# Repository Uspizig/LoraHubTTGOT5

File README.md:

# LoraHubTTGOT5
Please keep in mind. There are some Limitations in the TTn network right now:
1. For usage with TTN V3: Pease consider this change to avoid unwanted Downlink messages. https://github.com/mcci-catena/arduino-lmic/issues/713 

(Prerequisite: This is my Hobby: No Guarantee for HW or SW. I do not take any responsibility or will help you. This is: "Take it as it is or leave it".)
DO NOT USE THIS in ANY COMMERCIAL PRODUCTS

A LORA TTN Daughter Board for a TTGO T5 Board (http://s.click.aliexpress.com/e/NPRqgBkG) with BME680, BME280, CCS811 and connection possibilities for several other I²C Boards

You might have seen several E-Ink Boards from Waveshare lately. I came across some Boards from TTGO with an ESP32 lately on Aliexpress.
While experimenting with these Boards I tought: Why not add a LORA TTN Chip to these Boards and some other environment sensors.

So here is my try:

You may find in this Repository:
1. Hardware: KiCad & Gerber Files for 
2. SMT Assembly Files for jlcPCB 
3. Pinning: Pin Description
4. Software: A how to make these things running relatively easy in an Arduino IDE

What you need to do to get the SW Running:
1. Clone this Git: https://github.com/ZinggJM/GxEPD2 and install to your Arduino lib folder
2. Replace the two files with the ones provided in GxEPDReplace
3. Install: https://github.com/thesolarnomad/lora-serialization
4. Clone this Git: https://github.com/mcci-catena/arduino-lmic
5A. Make the modifications mentioned in otta SW
5B. Edidt config in the MCCI-Catena to set according yoru Country.
6. Get an App ID, from Thethingsnetwork
7. Check if your area has LORA TTN Coverage
8. Try out one of the examples.

What you need to get the HW:
- TTGO T5 EPaper Board: https://de.aliexpress.com/item/32869729970.html
- RFM95 Lora Chip: https://de.aliexpress.com/item/32831799362.html
- Antenna Connector SMA: http://s.click.aliexpress.com/e/5oGOCiY0
- (OPTIONAL)8dBi Antenna 868MHz: http://s.click.aliexpress.com/e/KVkmsTGG
- (OPTIONAL)TPL5110 for Low Power: http://s.click.aliexpress.com/e/EA7q1R48
- Spacer-Screws: http://s.click.aliexpress.com/e/KejkugSM

Hub Board:
1. Download the Gerber and BOM Files
2. Upload to JLCPCB
3. Select SMT Assembly
4. Solder 3 Diodes, Antenna Connector and RFM Module on the Board
5. (Optional): Solder Battery Connector and TPL5110 Chip on the Board.
6. I made a mistake on the FET and switched Drain and Source pin. You need to make a air wire to fix this if you want to use the TPL5110 RTC.

What you need to Solder
1. RFM95 Chip
2. Antenna Connector
3. 3x Diodes
(Optional) TPL5110 Chip and Battery Connector

Housings:
https://www.thingiverse.com/thing:3462483
https://www.thingiverse.com/thing:4055993

Useful Equipment.:
- Soldering Iron TS100: http://s.click.aliexpress.com/e/Eq2v9g12
- USB Cable: http://s.click.aliexpress.com/e/NiloJfUM
- Soldering Mat. http://s.click.aliexpress.com/e/NAoYAQ5K

My projects are influenced by Dave(G6EJD) and Andreas Spiess. So do me a favor and watch their videos.

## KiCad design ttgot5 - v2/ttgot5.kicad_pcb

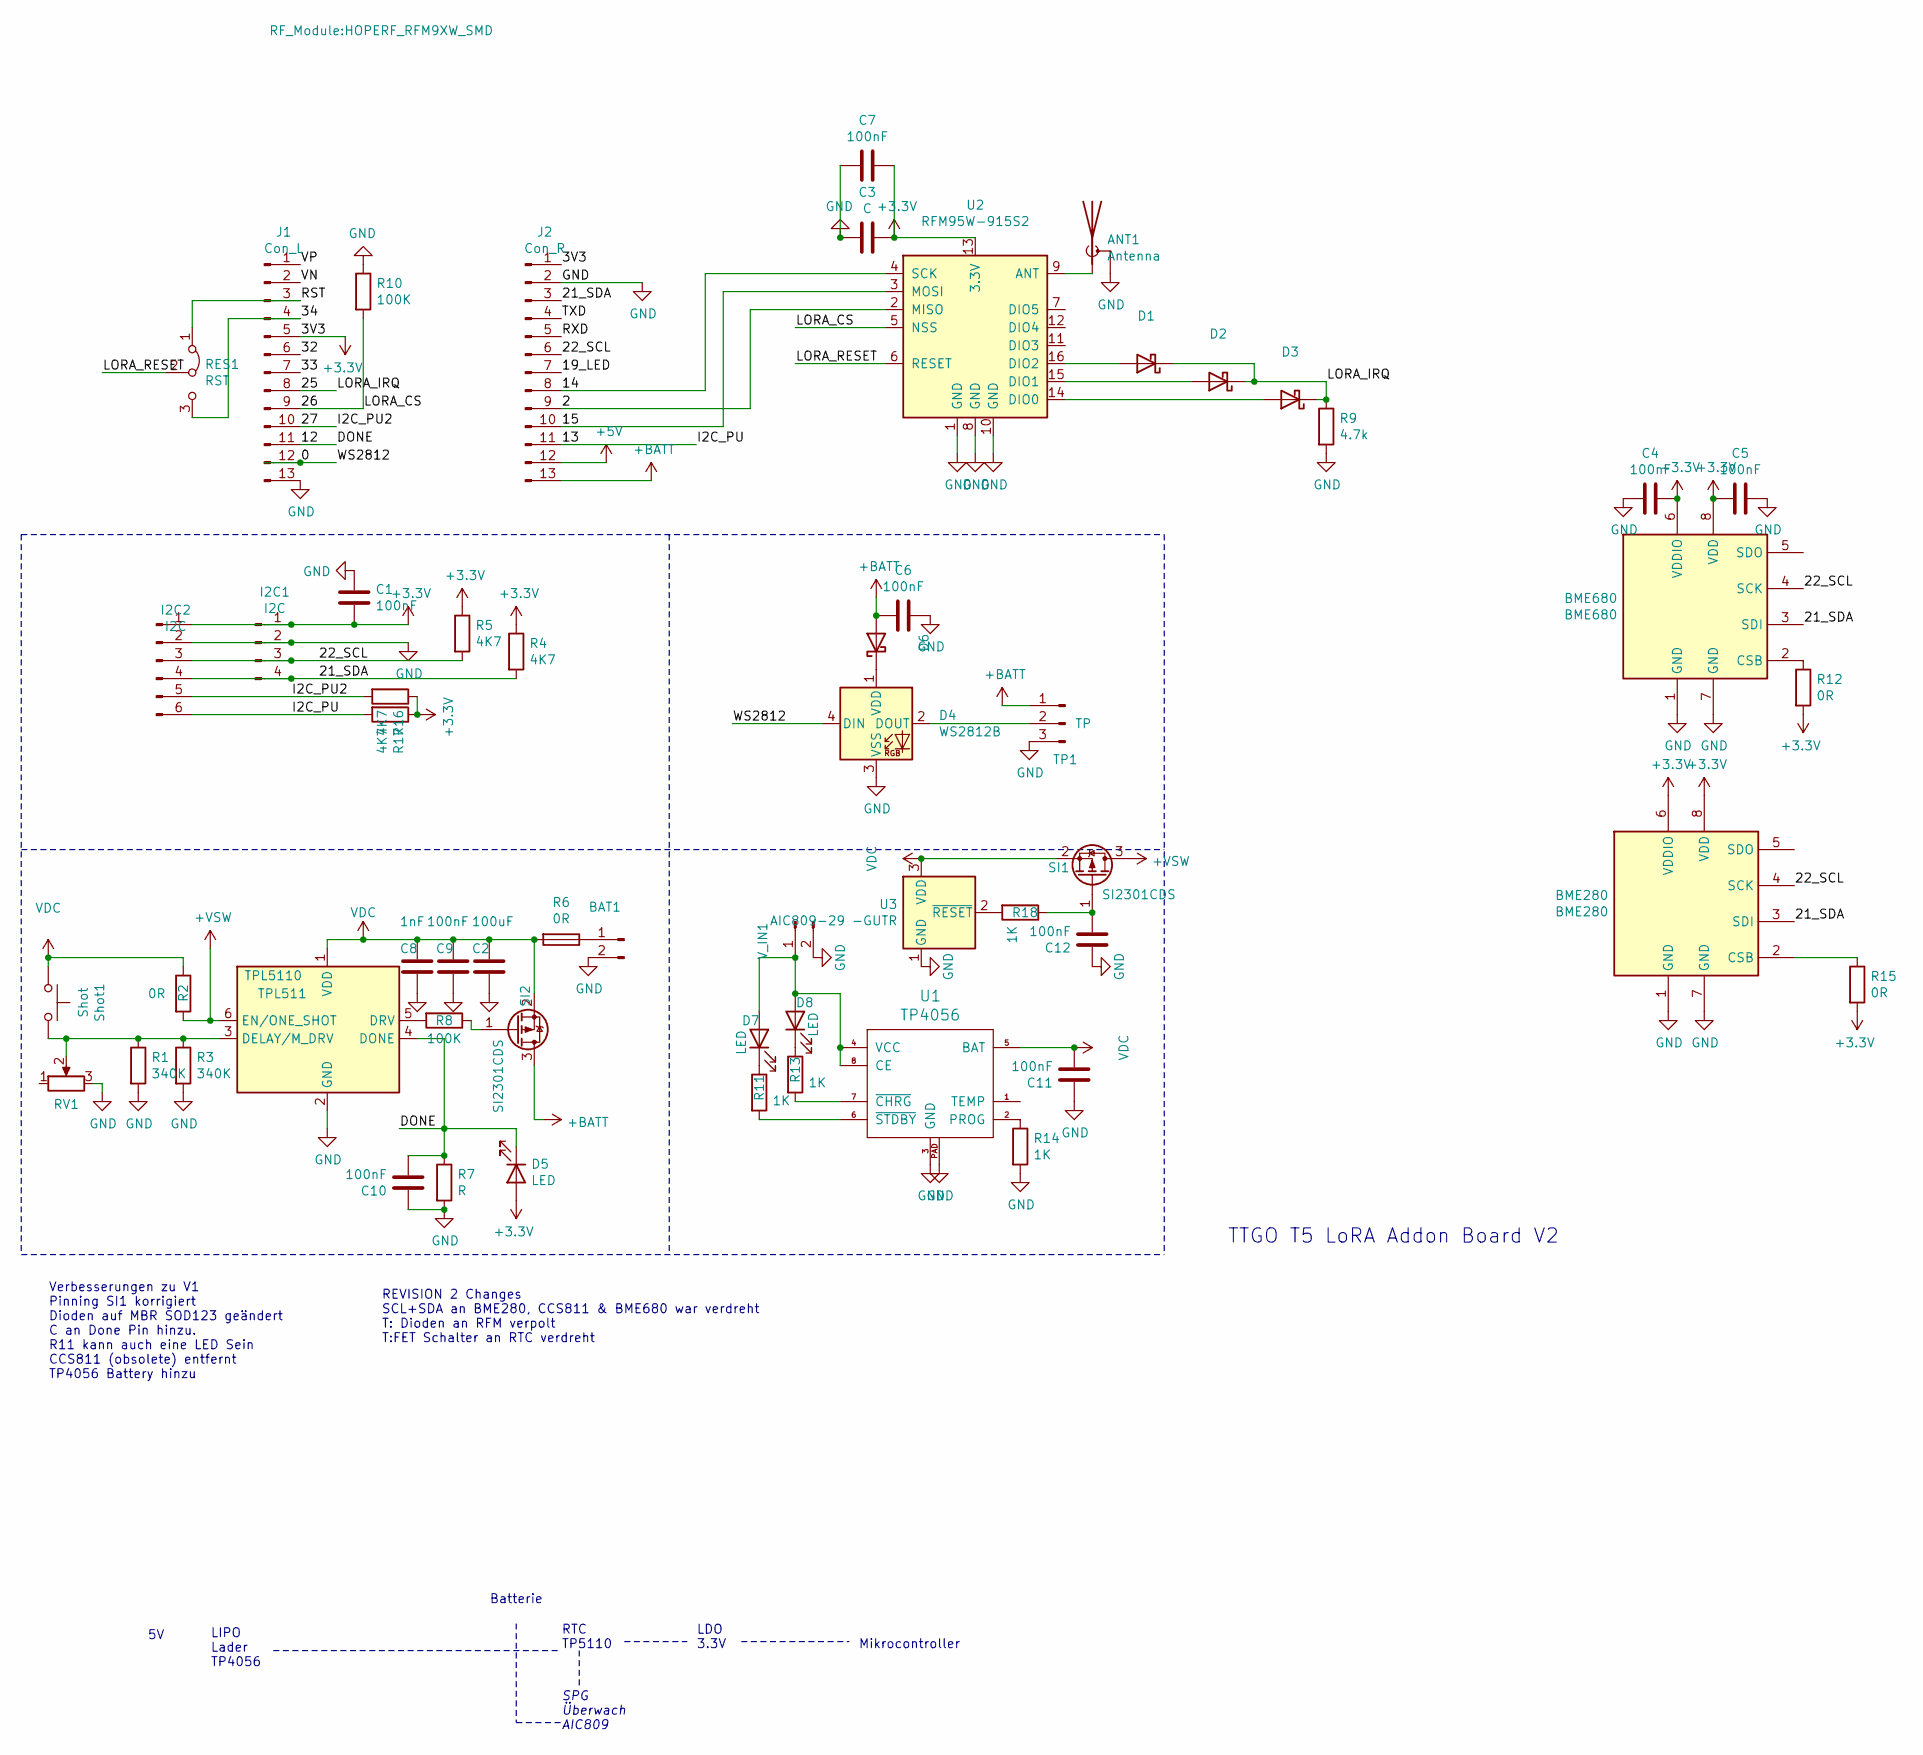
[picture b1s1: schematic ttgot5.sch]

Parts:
ANT1: Antenna; SMA_Samtec_SMA-J-P-H-ST-EM1_EdgeMount
BAT1: PWR; PinHeader_1x02_P2.54mm_Horizontal
BME280: BME280; Bosch_LGA-8_2.5x2.5mm_P0.65mm_ClockwisePinNumbering
BME680: BME680; Bosch_LGA-8_3x3mm_P0.8mm_ClockwisePinNumbering
C1, C4, C5, C6, C7, C9, C10, C11, C12: 100nF; C_0805_2012Metric_Pad1.15x1.40mm_HandSolder
C2: 100uF; C_0805_2012Metric_Pad1.15x1.40mm_HandSolder
C3: C; C_0805_2012Metric_Pad1.15x1.40mm_HandSolder
C8: 1nF; C_0805_2012Metric_Pad1.15x1.40mm_HandSolder
D1, D2, D3, D6: D; D_SOD-123
D4: WS2812B; LED_WS2812B_PLCC4_5.0x5.0mm_P3.2mm
D5, D7, D8: LED; LED_0805_2012Metric
I2C1: I2C; PinHeader_1x04_P2.54mm_Vertical
I2C2: I2C; PinHeader_1x06_P2.54mm_Vertical
J1: Con_L; PinHeader_1x13_P2.54mm_Vertical
J2: Con_R; PinHeader_1x13_P2.54mm_Vertical
R1, R3: 340K; R_0805_2012Metric_Pad1.15x1.40mm_HandSolder
R2, R6, R12, R15: 0R; R_0805_2012Metric_Pad1.15x1.40mm_HandSolder
R4, R5, R16, R17: 4K7; R_0805_2012Metric_Pad1.15x1.40mm_HandSolder
R7: R; R_0805_2012Metric_Pad1.15x1.40mm_HandSolder
R8, R10: 100K; R_0805_2012Metric_Pad1.15x1.40mm_HandSolder
R9: 4.7k; R_0805_2012Metric_Pad1.15x1.40mm_HandSolder
R11, R13, R14, R18: 1K; R_0805_2012Metric_Pad1.15x1.40mm_HandSolder
RES1: RST; SolderJumper-3_P1.3mm_Bridged12_Pad1.0x1.5mm
RV1: R_POT; Potentiometer_Bourns_3224W_Vertical
SI1, SI2: SI2301CDS; SOT-23
Shot1: Shot; PinHeader_1x02_P2.54mm_Horizontal
TP1: TP; PinHeader_1x03_P2.54mm_Vertical
TPL511: TPL5110; SOT-23-6
U1: TP4056; tp4056
U2: RFM95W-915S2; HOPERF_RFM9XW_SMD
U3: AIC809-29 -GUTR; SOT-23
V_IN1: PWR; PinHeader_1x02_P2.54mm_Horizontal

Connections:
+3V3: BME280.6 (VDDIO), BME280.8 (VDD), BME680.6 (VDDIO), BME680.8 (VDD), C1.2, C3.2, C4.1, C5.2, C7.2, D5.2 (A), I2C1.1, I2C2.1, J1.5, J2.1, R4.1, R5.1, R12.2, R15.2, R16.1, R17.1, U2.13 (3.3V)
+5V: J2.12
+BATT: C6.2, D6.2 (A), J2.13, SI2.3 (D), TP1.1
+VSW: R2.2, SI1.3 (D), TPL511.6 (EN/ONE_SHOT)
/0: D4.4 (DIN), J1.12
/2: J2.9, U2.2 (MISO)
/12: C10.2, D5.1 (K), J1.11, R7.1, TPL511.4 (DONE)
/13: I2C2.6, J2.11, R17.2
/14: J2.8, U2.4 (SCK)
/15: J2.10, U2.3 (MOSI)
/19_LED: J2.7
/21_SDA: BME280.3 (SDI), BME680.3 (SDI), I2C1.4, I2C2.4, J2.3, R4.2
/22_SCL: BME280.4 (SCK), BME680.4 (SCK), I2C1.3, I2C2.3, J2.6, R5.2
/25: D1.1 (K), D2.1 (K), D3.1 (K), J1.8, R9.1
/26: J1.9, R10.2, U2.5 (NSS)
/27: I2C2.5, J1.10, R16.2
/32: J1.6
/33: J1.7
/34: J1.4, RES1.3 (B)
/LORA_RESET: RES1.2 (C), U2.6 (RESET)
/RST: J1.3, RES1.1 (A)
/RXD: J2.5
/TXD: J2.4
/VN: J1.2
/VP: J1.1
GND: ANT1.2 (Shield), BAT1.2, BME280.1 (GND), BME280.7 (GND), BME680.1 (GND), BME680.7 (GND), C1.1, C2.2, C3.1, C4.2, C5.1, C6.1, C7.1, C8.2, C9.2, C10.1, C11.1, C12.1, D4.3 (VSS), I2C1.2, I2C2.2, J1.13, J2.2, R1.2, R3.2, R7.2, R9.2, R10.1, R14.2, RV1.3, TP1.3, TPL511.2 (GND), U1.3 (GND), U1.PAD, U2.1 (GND), U2.8 (GND), U2.10 (GND), U3.1 (GND), V_IN1.2
unnamed: ANT1.1 (A), U2.9 (ANT)
unnamed: BAT1.1, R6.1
unnamed: BME280.2 (CSB), R15.1
unnamed: BME680.2 (CSB), R12.1
unnamed: C12.2, R18.1, SI1.1 (G)
unnamed: D1.2 (A), U2.16 (DIO2)
unnamed: D2.2 (A), U2.15 (DIO1)
unnamed: D3.2 (A), U2.14 (DIO0)
unnamed: D4.1 (VDD), D6.1 (K)
unnamed: D4.2 (DOUT), TP1.2
unnamed: D7.1 (K), R11.1
unnamed: D7.2 (A), D8.2 (A), U1.4 (VCC), U1.8 (CE), V_IN1.1
unnamed: D8.1 (K), R13.1
unnamed: R1.1, R3.1, RV1.2, Shot1.1, TPL511.3 (DELAY/M_DRV)
unnamed: R8.1, SI2.1 (G)
unnamed: R8.2, TPL511.5 (DRV)
unnamed: R11.2, U1.6 (~STDBY)
unnamed: R13.2, U1.7 (~CHRG)
unnamed: R14.1, U1.2 (PROG)
unnamed: R18.2, U3.2 (~RESET)
VDC: C2.1, C8.1, C9.1, C11.2, R2.1, R6.2, SI1.2 (S), SI2.2 (S), Shot1.2, TPL511.1 (VDD), U1.5 (BAT), U3.3 (VDD)

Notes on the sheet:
REVISION 2 Changes SCL+SDA an BME280, CCS811 & BME680 war verdreht T: Dioden an RFM verpolt T:FET Schalter an RTC verdreht
Verbesserungen zu V1 Pinning SI1 korrigiert Dioden auf MBR SOD123 geändert C an Done Pin hinzu. R11 kann auch eine LED Sein CCS811 (obsolete) entfernt TP4056 Battery hinzu
TTGO T5 LoRA Addon Board V2
LIPO Lader TP4056
SPG Überwach AIC809
RTC TP5110
LDO 3.3V
Mikrocontroller
Batterie

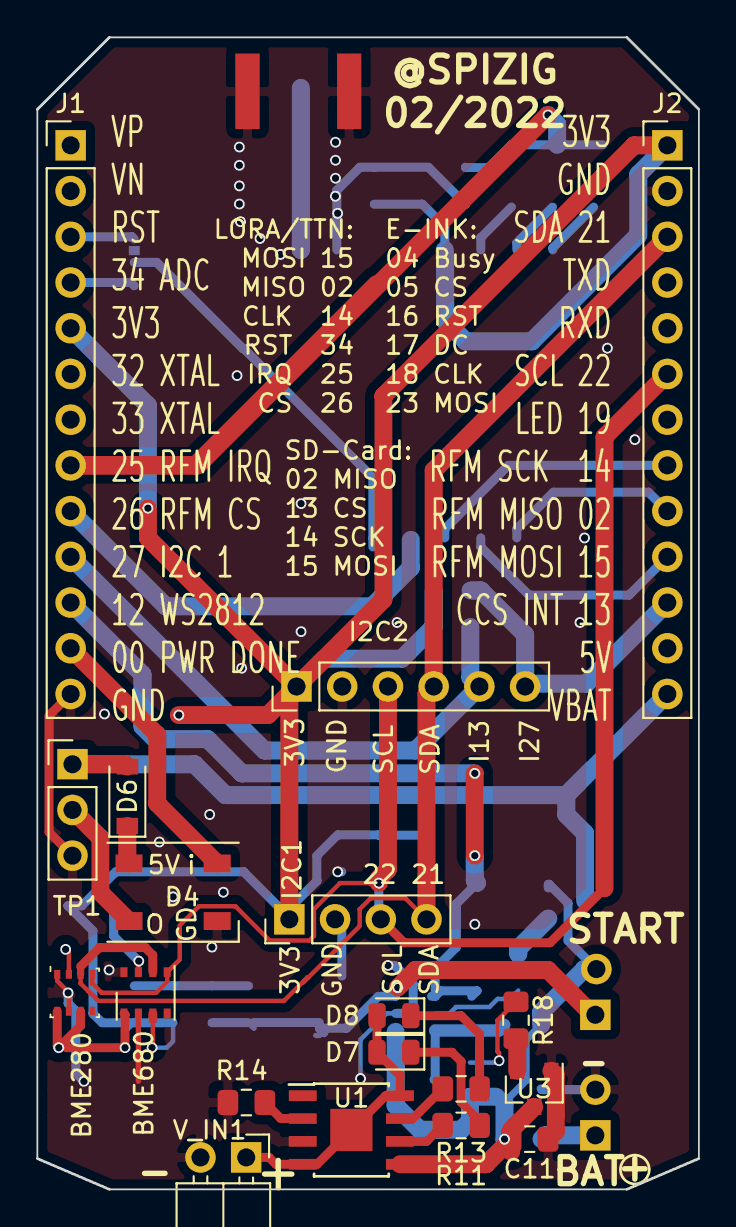
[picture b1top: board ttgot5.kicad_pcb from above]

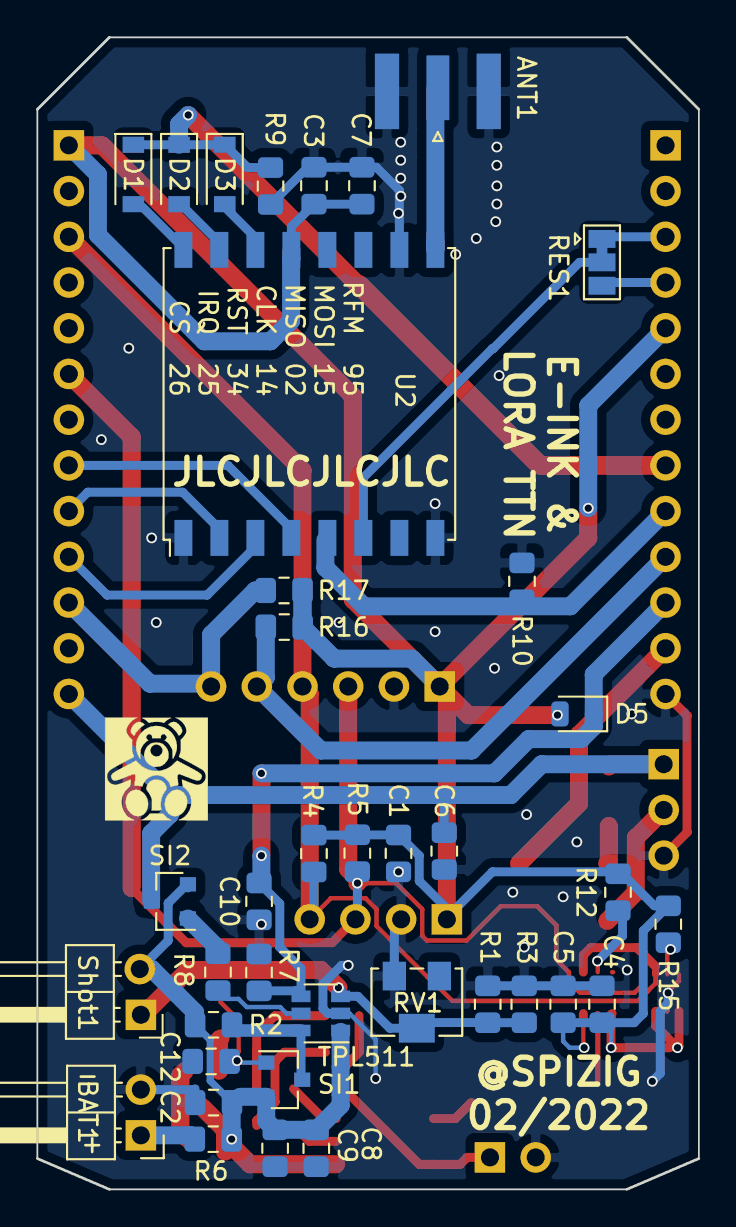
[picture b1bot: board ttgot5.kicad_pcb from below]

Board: 2 copper layers, 36.8 x 64.0 mm, 57 parts (38 on the bottom side), 39 nets.

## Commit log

2020-01-17 Add files via upload
    fixed long TX Delays
